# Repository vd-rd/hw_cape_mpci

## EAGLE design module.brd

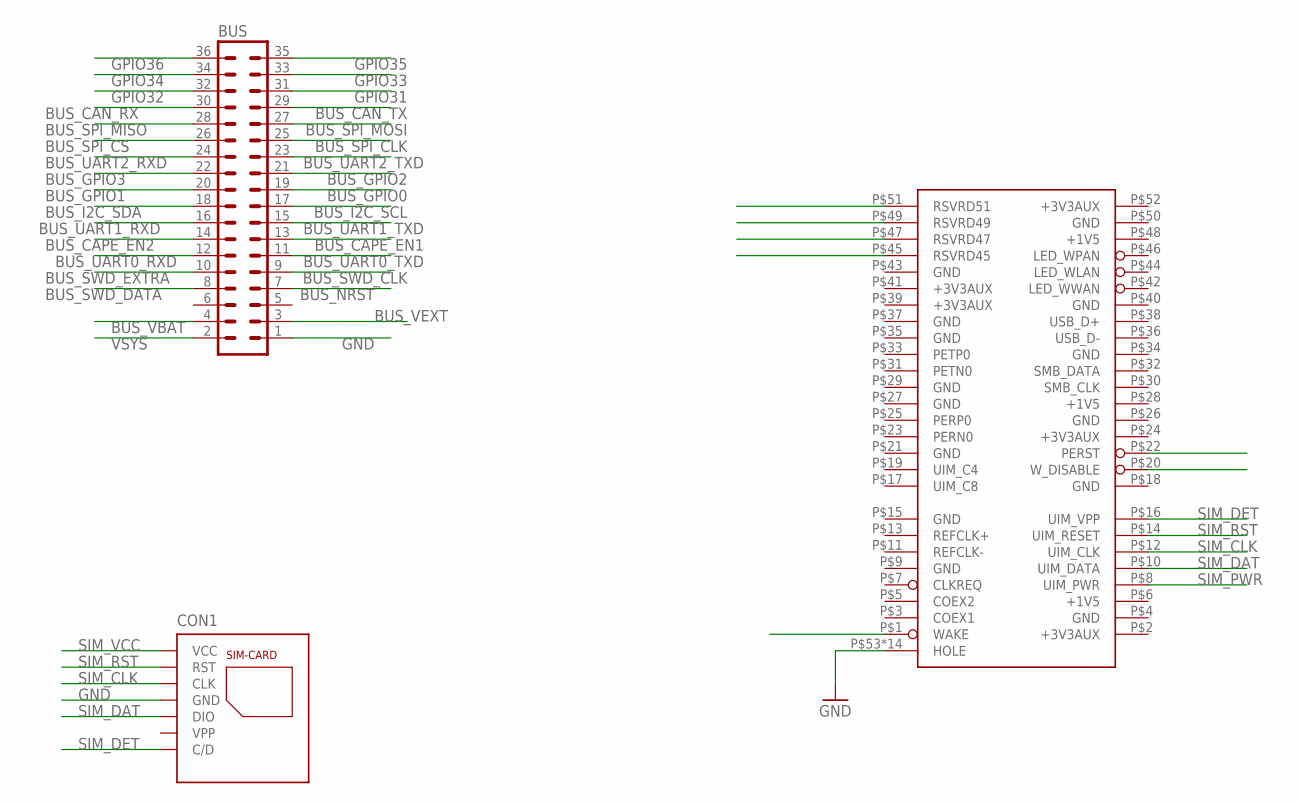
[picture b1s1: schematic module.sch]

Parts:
BUS: MA18-2
CON1: 115Q-BCA0; 115Q
PCI1: 119A-XXA00; 119A

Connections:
+1V5: PCI1.P$6 (+1V5), PCI1.P$28 (+1V5)
+3V3AUX: PCI1.P$2 (+3V3AUX), PCI1.P$24 (+3V3AUX), PCI1.P$52 (+3V3AUX)
BUS_CAN_RX: BUS.30
BUS_CAN_TX: BUS.29
BUS_CAPE_EN1: BUS.13
BUS_CAPE_EN2: BUS.14
BUS_GPIO0: BUS.19
BUS_GPIO1: BUS.20
BUS_GPIO2: BUS.21
BUS_GPIO3: BUS.22
BUS_I2C_SCL: BUS.17
BUS_I2C_SDA: BUS.18
BUS_NRST: BUS.7
BUS_SPI_CLK: BUS.25
BUS_SPI_CS: BUS.26
BUS_SPI_MISO: BUS.28
BUS_SPI_MOSI: BUS.27
BUS_SWD_CLK: BUS.9
BUS_SWD_DATA: BUS.8
BUS_SWD_EXTRA: BUS.10
BUS_UART0_RXD: BUS.12
BUS_UART0_TXD: BUS.11
BUS_UART1_RXD: BUS.16
BUS_UART1_TXD: BUS.15
BUS_UART2_RXD: BUS.24
BUS_UART2_TXD: BUS.23
BUS_VBAT: BUS.4
BUS_VEXT: BUS.3
GND: BUS.1, CON1.GND1 (GND), CON1.GND2 (GND), CON1.GND3 (GND), CON1.GND4 (GND), CON1.P5 (GND), PCI1.P$4 (GND), PCI1.P$9 (GND), PCI1.P$15 (GND), PCI1.P$18 (GND), PCI1.P$21 (GND), PCI1.P$26 (GND), PCI1.P$27 (GND), PCI1.P$29 (GND), PCI1.P$35 (GND), PCI1.P$53 (HOLE), PCI1.P$54 (HOLE), PCI1.P$55 (HOLE), PCI1.P$56 (HOLE), PCI1.P$57 (HOLE), PCI1.P$58 (HOLE), PCI1.P$59 (HOLE), PCI1.P$60 (HOLE), PCI1.P$61 (HOLE), PCI1.P$62 (HOLE), PCI1.P$63 (HOLE), PCI1.P$64 (HOLE), PCI1.P$65 (HOLE), PCI1.P$66 (HOLE)
GPIO31: BUS.31
GPIO32: BUS.32
GPIO33: BUS.33
GPIO34: BUS.34
GPIO35: BUS.35
GPIO36: BUS.36
SIM_CLK: CON1.P3 (CLK), PCI1.P$12 (UIM_CLK)
SIM_DAT: CON1.P7 (DIO), PCI1.P$10 (UIM_DATA)
SIM_DET: CON1.CD (C/D), PCI1.P$16 (UIM_VPP)
SIM_PWR: PCI1.P$8 (UIM_PWR)
SIM_RST: CON1.P2 (RST), PCI1.P$14 (UIM_RESET)
SIM_VCC: CON1.P1 (VCC)
SMB_DATA: PCI1.P$32 (SMB_DATA)
USB_D+: PCI1.P$38 (USB_D+)
VSYS: BUS.2

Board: 2 copper layers, 3 parts (1 on the bottom side), 7 nets, no tracks yet.

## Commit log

2019-05-02 project: add cad files
